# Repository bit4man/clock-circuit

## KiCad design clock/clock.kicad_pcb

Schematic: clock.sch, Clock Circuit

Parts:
C1: 1uF; CP_Radial_D5.0mm_P2.50mm
C2: 100uF; CP_Radial_D5.0mm_P2.50mm
C3: 330nF; CP_Radial_D5.0mm_P2.50mm
C4: 100nF; CP_Radial_D5.0mm_P2.50mm
C5, C6: 30pF; C_Disc_D3.8mm_W2.6mm_P2.50mm
C7: 1uF; CP_Radial_D4.0mm_P2.00mm
C8, C10, C11, C13: 10pF; C_Disc_D3.8mm_W2.6mm_P2.50mm
C12: 10uF; CP_Radial_D4.0mm_P2.00mm
D1, D2, D3, D5, D6, D7, D8, D9, D10, D11, D12, D13, D15: LED_Small; LED_D4.0mm
D4, D16: D; D_DO-41_SOD81_P7.62mm_Horizontal
J1: Barrel_Jack; BarrelJack_Horizontal
J2: Conn_01x04; JST_EH_B5B-EH-A_1x05_P2.50mm_Vertical
J3: Power +5V In; JST_EH_B2B-EH-A_1x02_P2.50mm_Vertical
Q1, Q2, Q3, Q4: 2N3904; TO-92_Inline
R1, R8, R9, R13, R15: 10K; R_Axial_DIN0207_L6.3mm_D2.5mm_P7.62mm_Horizontal
R2, R3, R10: 150; R_Axial_DIN0207_L6.3mm_D2.5mm_P7.62mm_Horizontal
R4, R5, R12, R21: 100K; R_Axial_DIN0207_L6.3mm_D2.5mm_P7.62mm_Horizontal
R6, R7, R11: 2K; R_Axial_DIN0207_L6.3mm_D2.5mm_P7.62mm_Horizontal
R14, R16, R17, R18, R19, R20: 1K; R_Axial_DIN0207_L6.3mm_D2.5mm_P7.62mm_Horizontal
RN1, RN2: 470; R_Array_SIP5
RN3: 10K; R_Array_SIP5
RV1: 500K; Potentiometer_ACP_CA9-H5_Horizontal
SW1: SW_Clock; SW_PUSH_6mm
SW2: CLK_SEL; SW_DIP_SPSTx02_Slide_9.78x7.26mm_W7.62mm_P2.54mm
SW3: SW_Step; SW_PUSH_6mm
SW4: SW_MANUAL_CLK; SW_PUSH_6mm
U1: LM7805; TO-220-3_Vertical
U2: 74LS93; DIP-14_W7.62mm_Socket
U3: LM556; DIP-14_W7.62mm_Socket
U4: 74LS151; DIP-16_W7.62mm_Socket
U5: 74LS08; DIP-14_W7.62mm_Socket
U6: 74LS32; DIP-14_W7.62mm_Socket
U8: 74LS04; DIP-14_W7.62mm_Socket
U9: 74LS00; DIP-14_W7.62mm_Socket
U10: LM555; DIP-8_W7.62mm_Socket

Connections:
+5V: C4.1, C8.2, C10.2, C11.2, C13.2, D4.1 (K), J3.1, Q1.3, Q2.3, Q3.3, Q4.3, R1.2, R9.1, R12.2, R13.2, SW2.1, SW2.2, SW3.2, U1.3 (VO), U2.5 (VCC), U3.14 (VCC), U4.16 (VCC), U5.14, U6.14 (VCC), U8.14 (VCC), U9.14 (VCC), U10.4 (R), U10.8 (VCC)
AEN: C2.1, D1.2 (A), R3.2, R21.1, U3.5 (Q), U3.10 (R)
AFREQ: D16.1 (K), R15.1, SW3.1, U4.4 (I0), U9.10
ATHR: C7.1, RV1.2, U3.8 (TR), U3.12 (THR)
BTHR: R1.1, R8.1, SW1.2, U3.2 (THR), U3.6 (TR)
CLK: U2.14 (CP0), U4.5 (Z), U6.1, U9.2
GND: C1.2, C3.2, C4.2, C5.2, C6.2, C7.2, C8.1, C10.1, C11.1, C12.2, C13.1, D4.2 (A), D8.1 (K), J1.2, J2.1, J3.2, R2.2, R3.1, R4.2, R5.2, R6.2, R7.2, R8.2, R11.2, R14.2, R15.2, R16.1, RN1.1 (common), RN2.1 (common), RN3.1 (common), SW4.2, U1.2 (GND), U2.10 (GND), U3.1 (DIS), U3.7 (GND), U4.2 (I2), U4.7 (~E), U4.8 (GND), U4.9 (S2), U4.12 (I7), U4.13 (I6), U4.14 (I5), U4.15 (I4), U5.7, U6.7 (GND), U8.7 (GND), U9.7 (GND), U10.1 (GND)
MFREQ: D15.2 (A), U4.3 (I1), U10.3 (Q)
unnamed: C1.1, R21.2, SW1.1
unnamed: C2.2, R16.2, U2.2 (R0(1)), U2.3 (R0(2))
unnamed: C5.1, U3.3 (CV)
unnamed: C6.1, U3.11 (CV)
unnamed: C12.1, R13.1, U10.6 (THR), U10.7 (DIS)
unnamed: D1.1 (K), R2.1
unnamed: D2.1 (K), R6.1
unnamed: D2.2 (A), R4.1, SW2.3, U4.10 (S1)
unnamed: D3.1 (K), R7.1
unnamed: D3.2 (A), R5.1, SW2.4, U4.11 (S0)
unnamed: D5.1 (K), RN1.3 (R2)
unnamed: D6.1 (K), RN1.4 (R3)
unnamed: D7.1 (K), RN1.5 (R4)
unnamed: D8.2 (A), R10.2
unnamed: D9.1 (K), R11.1
unnamed: D10.1 (K), RN2.2 (R1)
unnamed: D10.2 (A), R17.2, U5.3
unnamed: D11.1 (K), RN2.3 (R2)
unnamed: D11.2 (A), R18.2, U5.6
unnamed: D12.1 (K), RN2.4 (R3)
unnamed: D12.2 (A), R19.2, U5.8
unnamed: D13.1 (K), RN2.5 (R4)
unnamed: D13.2 (A), R20.2, U5.11
unnamed: D15.1 (K), R14.1
unnamed: D9.2 (A), D16.2 (A), U3.9 (Q)
unnamed: J2.2, Q1.1, RN3.5 (R4)
unnamed: J2.3, Q2.1, RN3.4 (R3)
unnamed: J2.4, Q3.1, RN3.3 (R2)
unnamed: J2.5, Q4.1, RN3.2 (R1)
unnamed: Q1.2, R20.1
unnamed: Q2.2, R19.1
unnamed: Q3.2, R18.1
unnamed: Q4.2, R17.1
unnamed: R9.2, RV1.3, U3.13 (DIS)
unnamed: R10.1, U8.10
unnamed: R12.1, SW4.1, U10.2 (TR)
unnamed: U5.1, U5.9, U8.2
unnamed: U5.2, U5.5, U8.6
unnamed: U5.4, U5.12, U8.4
unnamed: U6.2, U9.6
unnamed: U6.3, U8.3
unnamed: U6.6, U6.9
unnamed: U6.8, U8.11, U9.9
unnamed: U8.1, U9.1, U9.11
unnamed: U8.9, U9.8
unnamed: U9.3, U9.12
PUL0: D7.2 (A), U2.1 (CP1..3), U2.12 (Q0), U6.4, U9.5
PUL1: D6.2 (A), U2.9 (Q1), U6.5, U9.4, U9.13
PUL2: D5.2 (A), U2.8 (Q2), U5.10, U5.13, U6.10, U8.5
STEP: U4.1 (I3), U8.8
VCC: C3.1, J1.1, U1.1 (VI)

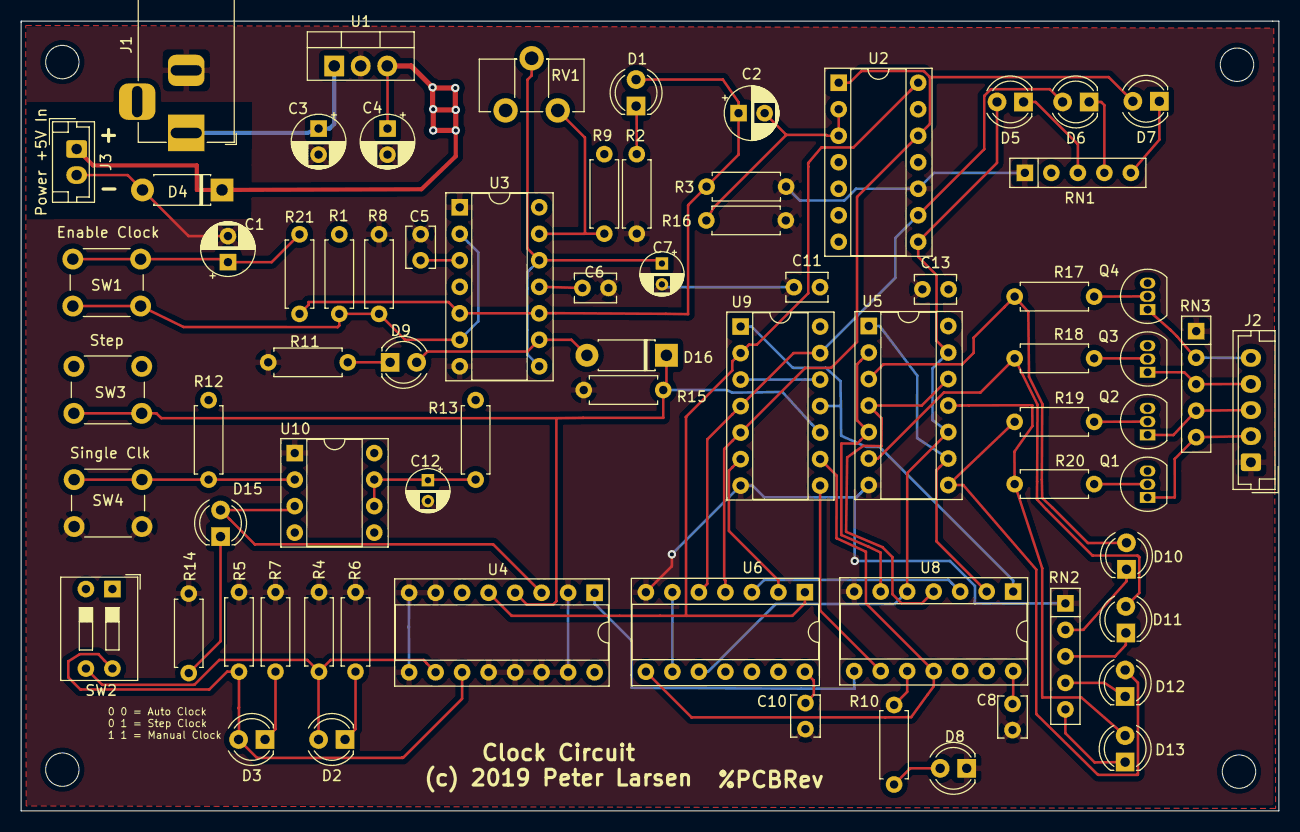
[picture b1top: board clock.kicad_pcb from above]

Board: 2 copper layers, 120.5 x 75.7 mm, 72 parts (0 on the bottom side), 59 nets.

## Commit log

2019-08-08 Added .gitignore
2019-08-08 Removed backup and temporary files from git
2019-08-16 Added switches and redesign
2019-08-16 Reduced/condensed size - added mounting holes
2019-08-26 Fixed plug sizes and foot prints
2019-08-26 Corrected LM556 toggle switch circuit

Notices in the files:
clock/clock.kicad_pcb:
(c) 2019 Peter Larsen
